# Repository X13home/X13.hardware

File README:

X13.hardware
===========

Hardware section for project X13.Home.
Automation System oriented to "Smart House" over MQTT(S) protocol

Bridge        Bridges between protocols and bus's
Mainboards    Transceivers, Nodes/Gateways and accessories
Obsolete      No comments
Other         Expansions module, modular 72mm series
Sensors       Sensors, Temperature Humidity Pressure ...

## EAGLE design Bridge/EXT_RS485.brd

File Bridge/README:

X13.hardware.Bridge
===================

Bridges between protocols and bus's

Bridge_PCA9517      I2C to I2C Bridge/Level Translator
EXT_RS485           Adapter to RS485 Bus, Modular 72mm Series
EXT_TWI_LVC         I2C to I2C Bridge/Level Translator, Modular 72mm Series
USB_Adapter         USB Adapter to UART adapter 20 pin

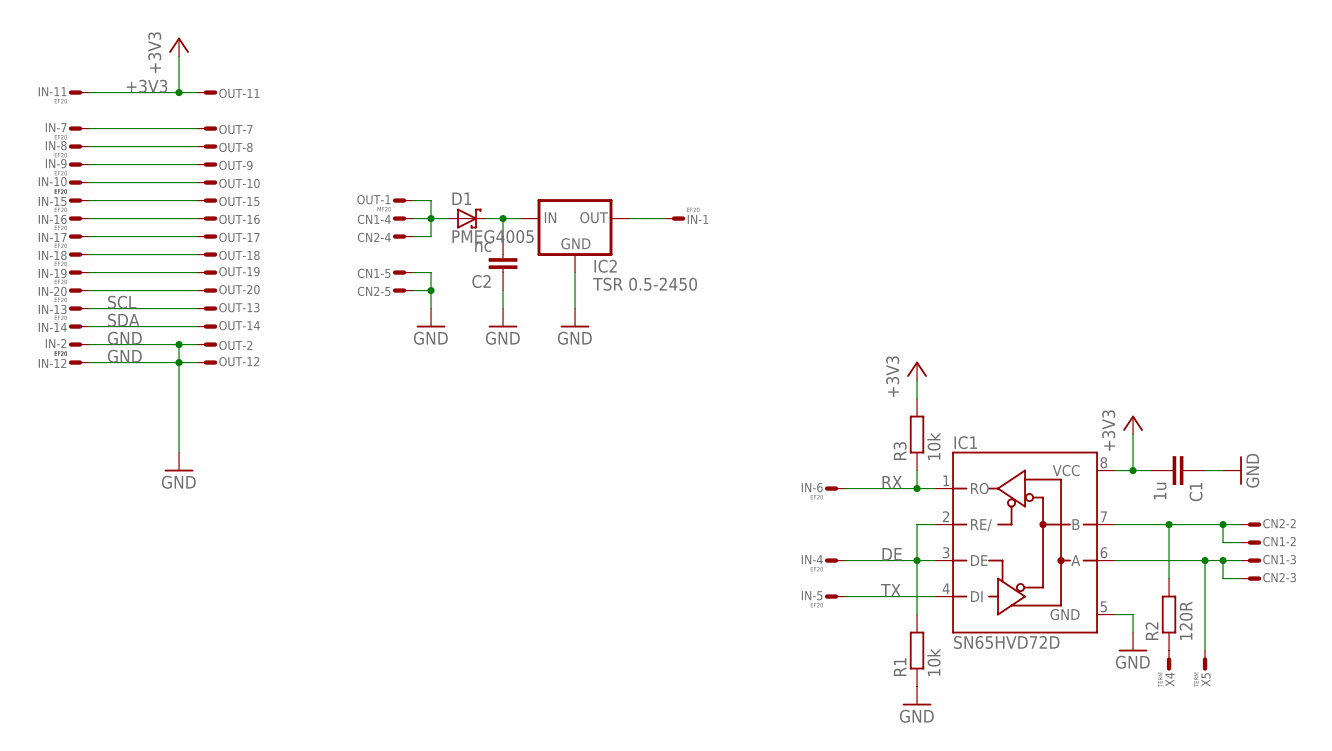
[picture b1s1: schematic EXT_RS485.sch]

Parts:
C1: 1u; 0603
C2: nc; 1206
CN1, CN2: RJ11; 69254
D1: PMEG4005; SOD323
IC1: SN65HVD72D; SOIC8
IC2: TSR 0.5-2450; SIP3
IN: EF20; FE10-2WSS
OUT: MF20; ML20LS
R1, R3: 10k; 0603
R2: 120R; 0603
X4, X5: TERM; T1.6/0.9

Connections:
+3V3: C1.2, IC1.8 (VCC), IN.P$11, OUT.P$11, R3.2
BUS-A: CN1.-3, CN2.-3, IC1.6 (A), X5.1
BUS-B: CN1.-2, CN2.-2, IC1.7 (B), R2.2
BUS-R: R2.1, X4.1
DE: IC1.2 (RE/), IC1.3 (DE), IN.P$4, R1.2
GND: C1.1, C2.1, CN1.-5, CN2.-5, IC1.5 (GND), IC2.P$2 (GND), IN.P$2, IN.P$12, OUT.P$2, OUT.P$12, R1.1
unnamed: IN.P$7, OUT.P$7
unnamed: IN.P$8, OUT.P$8
unnamed: IN.P$9, OUT.P$9
unnamed: IN.P$10, OUT.P$10
unnamed: IN.P$20, OUT.P$20
unnamed: IN.P$19, OUT.P$19
unnamed: IN.P$18, OUT.P$18
unnamed: IN.P$17, OUT.P$17
unnamed: IN.P$16, OUT.P$16
unnamed: IN.P$15, OUT.P$15
unnamed: C2.2, D1.C, IC2.P$1 (IN)
RX: IC1.1 (RO), IN.P$6, R3.1
SCL: IN.P$13, OUT.P$13
SDA: IN.P$14, OUT.P$14
TX: IC1.4 (DI), IN.P$5
VIN: CN1.-4, CN2.-4, D1.A, OUT.P$1
VOUT: IC2.P$3 (OUT), IN.P$1

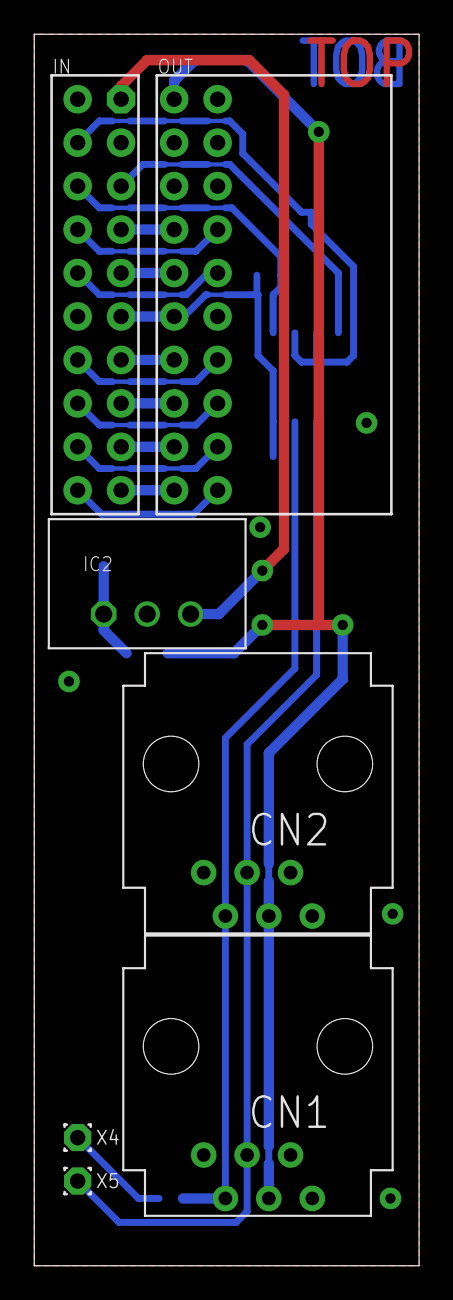
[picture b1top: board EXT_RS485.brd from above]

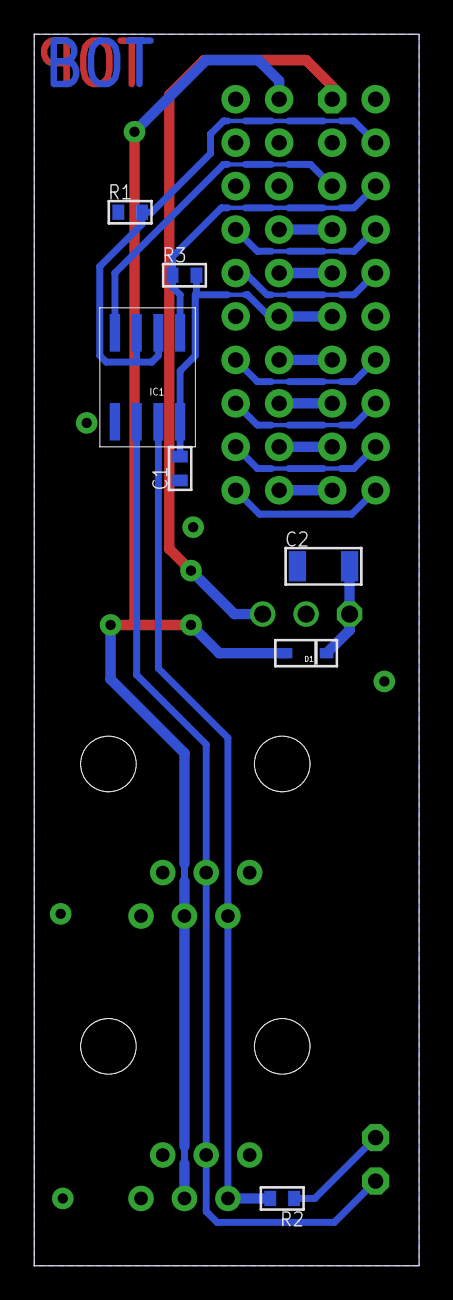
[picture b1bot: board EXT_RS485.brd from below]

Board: 2 copper layers, 22.5 x 72.0 mm, 14 parts (7 on the bottom side), 23 nets.

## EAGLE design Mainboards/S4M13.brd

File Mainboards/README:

X13.hardware.Mainboards
=======================

Hardware section for project X13.Home.

Automation System oriented to "Smart House"(IoT) over MQTT(SN) protocol

Universal
  S2EC13                Universal Mainboard, STM32Fxx + Board ENC28J60/UART-USB/RS485 + RF CC1101(TI), Format DIN 72mm.
  S2ER13                Universal Mainboard, STM32Fxx + Board ENC28J60/UART-USB/RS485 + RF RFM69CW, Format DIN 72mm.
  S2Mn10                Micro (33/19mm) RS485 node, STM32FxxxKxT
  S4Cx11                Mini Board STM32F3 + CC1101 Module
  S4Qx11                Mini Board STM32F3 + RFM69CW Module

RF only 433/868/915 MHz
  TRV_UP20              Mainboard UP20, ATMega328P + TRV CC1101(TI)
  TRV_MRF49_U_V1.1_F    Mainboard UN10, ATMega328P + TRV MRF49XA(Microchip)

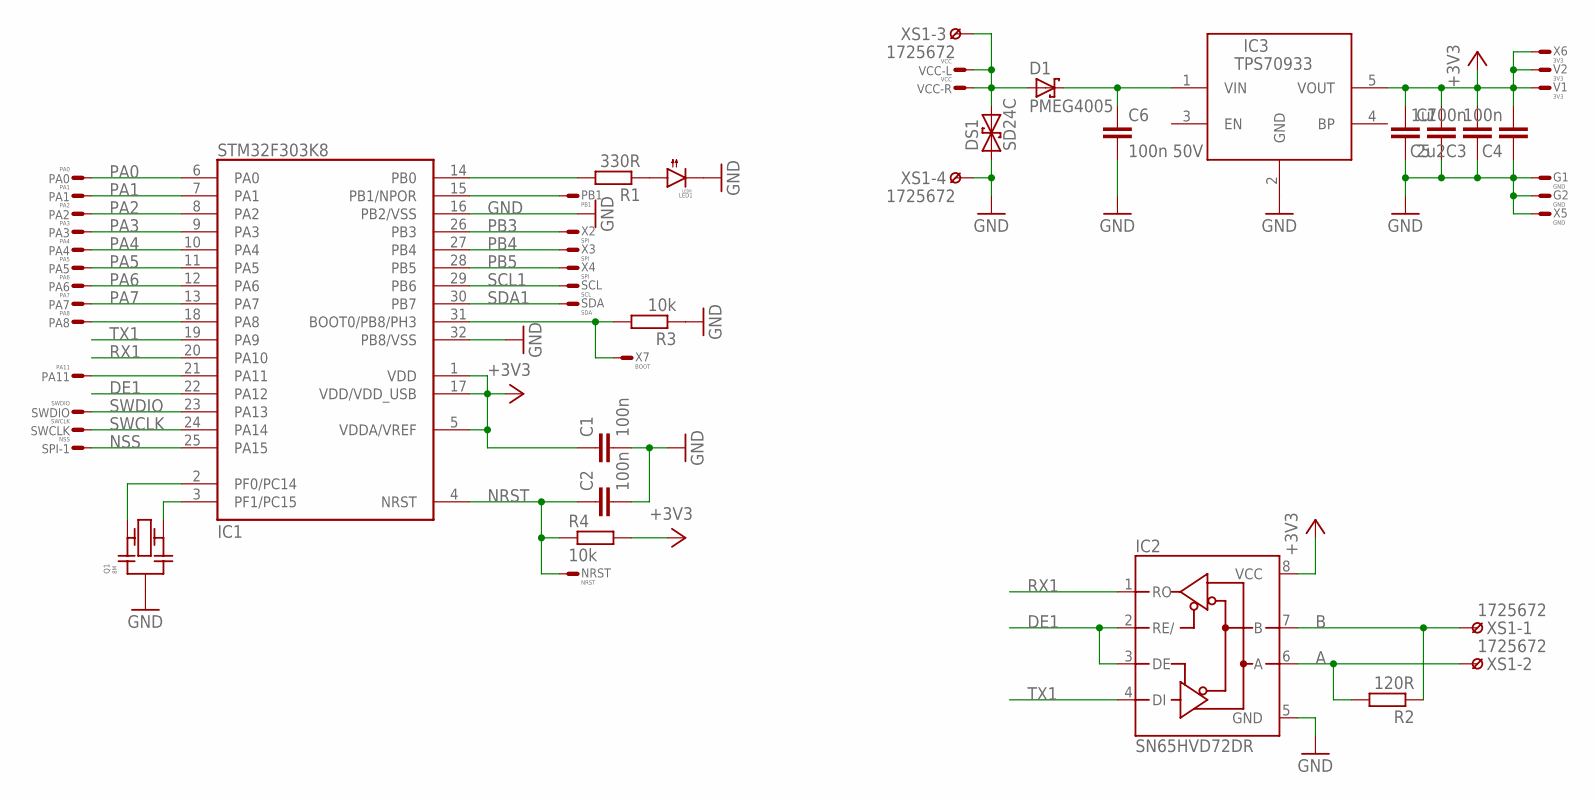
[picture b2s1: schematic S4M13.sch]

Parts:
C1, C2, C3, C4: 100n; 0603
C5: 1u; 0603
C6: 100n 50V; 0603
C7: 2u2; 0603
D1: PMEG4005; SOD323
DS1: SD24C; SOD323
G1, G2: GND; T1.6/0.9
IC1: STM32F303K8; LQFP32-7X7
IC2: SN65HVD72DR; SOIC8
IC3: TPS70933; SOT23-5
LED1: LEDR; 1206
NRST: NRST; T1.6/0.9
PA0: PA0; T1.6/0.9
PA1: PA1; T1.6/0.9
PA2: PA2; T1.6/0.9
PA3: PA3; T1.6/0.9
PA4: PA4; T1.6/0.9
PA5: PA5; T1.6/0.9
PA6: PA6; T1.6/0.9
PA7: PA7; T1.6/0.9
PA8: PA8; T1.6/0.9
PA11: PA11; T1.6/0.9
PB1: PB1; T1.6/0.9
Q1: 8M; CSTCE
R1: 330R; 0603
R2: 120R; 0603
R3, R4: 10k; 0603
SCL: SCL; T1.6/0.9
SDA: SDA; T1.6/0.9
SPI-1: NSS; S1.6/0.8
SWCLK: SWCLK; T1.6/0.9
SWDIO: SWDIO; T1.6/0.9
V1, V2: 3V3; T1.6/0.9
VCC-L: VCC; T1.6/0.9
VCC-R: VCC; T1.6/0.9
X2, X3, X4: SPI; S1.6/0.8
X5: GND; S1.6/0.8
X6: 3V3; S1.6/0.8
X7: BOOT; S1.27R
XS1: 1725672

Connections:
+3V3: C1.1, C3.2, C4.2, C5.2, C7.1, IC1.1 (VDD), IC1.5 (VDDA/VREF), IC1.17 (VDD/VDD_USB), IC2.8 (VCC), IC3.5 (VOUT), R4.2, V1.1, V2.1, X6.W
A: IC2.6 (A), R2.2, XS1.2
B: IC2.7 (B), R2.1, XS1.1
DE1: IC1.22 (PA12), IC2.2 (RE/), IC2.3 (DE)
GND: C1.2, C2.2, C3.1, C4.1, C5.1, C6.2, C7.2, DS1.A (1), G1.1, G2.1, IC1.16 (PB2/VSS), IC1.32 (PB8/VSS), IC2.5 (GND), IC3.2 (GND), LED1.2 (C), Q1.G (M), R3.1, X5.W, XS1.4
LED: IC1.14 (PB0), R1.2
unnamed: IC1.3 (PF1/PC15), Q1.B (2)
unnamed: IC1.31 (BOOT0/PB8/PH3), R3.2, X7.1
unnamed: IC1.2 (PF0/PC14), Q1.A (1)
unnamed: C6.1, D1.C, IC3.1 (VIN)
unnamed: LED1.1 (A), R1.1
NRST: C2.1, IC1.4 (NRST), NRST.1, R4.1
NSS: IC1.25 (PA15), SPI-1.W
PA0: IC1.6 (PA0), PA0.1
PA1: IC1.7 (PA1), PA1.1
PA2: IC1.8 (PA2), PA2.1
PA3: IC1.9 (PA3), PA3.1
PA4: IC1.10 (PA4), PA4.1
PA5: IC1.11 (PA5), PA5.1
PA6: IC1.12 (PA6), PA6.1
PA7: IC1.13 (PA7), PA7.1
PA8: IC1.18 (PA8), PA8.1
PA11: IC1.21 (PA11), PA11.1
PB1: IC1.15 (PB1/NPOR), PB1.1
PB3: IC1.26 (PB3), X2.W
PB4: IC1.27 (PB4), X3.W
PB5: IC1.28 (PB5), X4.W
RX1: IC1.20 (PA10), IC2.1 (RO)
SCL1: IC1.29 (PB6), SCL.1
SDA1: IC1.30 (PB7), SDA.1
SWCLK: IC1.24 (PA14), SWCLK.1
SWDIO: IC1.23 (PA13), SWDIO.1
TX1: IC1.19 (PA9), IC2.4 (DI)
VIN: D1.A, DS1.C (2), VCC-L.1, VCC-R.1, XS1.3

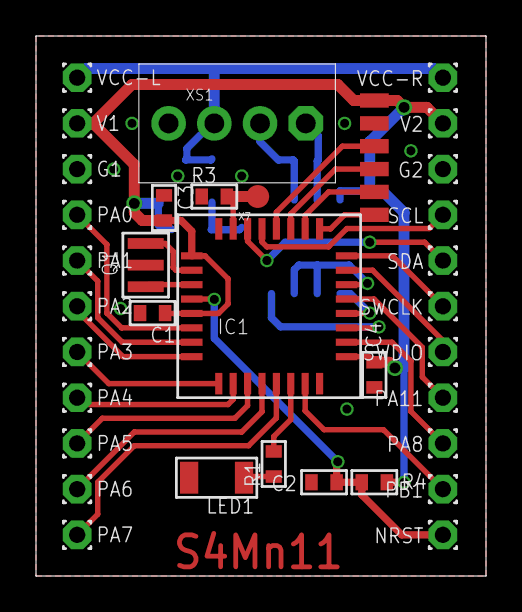
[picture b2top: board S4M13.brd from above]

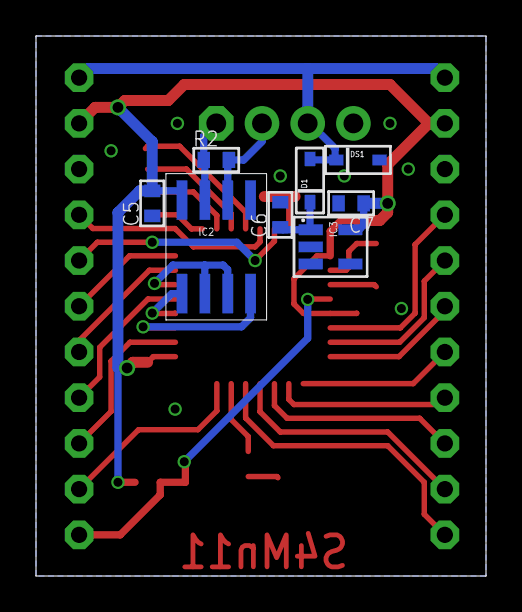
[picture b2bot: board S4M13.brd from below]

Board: 2 copper layers, 25.0 x 30.0 mm, 48 parts (8 on the bottom side), 34 nets.

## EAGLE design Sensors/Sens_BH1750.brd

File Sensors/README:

Sens_BH1750(small)          Sensor Rohm - BH1750, Ambient Light
Sens_BMP180                 Sensor Bosh - BMP180, Pressure & Temperature, compatible with BMP085
Sens_BME280                 Sensor Bosh - BME280, Pressure Temperature Humidity
Sens_CC2D                   Sensor ChipCap2 from "GE Measurement & Control", Temperature and Humidity
Sens_HIH613x                Sensors Honeywell - HIH6130/HIH6131, Temperature and Humidity
Sens_LM75                   Sensor NXP/NS/STmicro - LM75, Temperature
Sens_SHT2x                  Sensor Sensirion SHT21/SiLabs Si7020, Temperature and Humidity

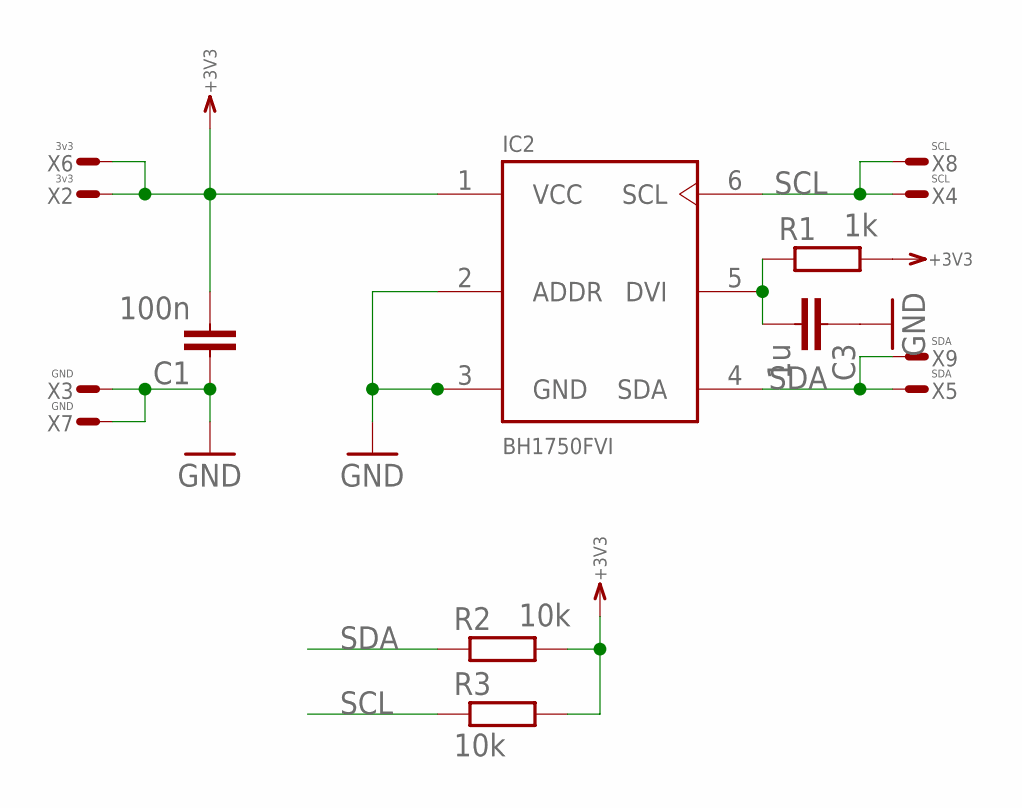
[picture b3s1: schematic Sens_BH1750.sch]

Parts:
C1: 100n; 0603
C3: 1u; 0603
IC2: BH1750FVI; WSOF6I
R1: 1k; 0603
R2, R3: 10k; 0603
X2, X6: 3v3; T1.6/0.9
X3, X7: GND; T1.6/0.9
X4, X8: SCL; T1.6/0.9
X5, X9: SDA; T1.6/0.9

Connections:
+3V3: C1.2, IC2.1 (VCC), R1.2, R2.2, R3.2, X2.1, X6.1
GND: C1.1, C3.1, IC2.2 (ADDR), IC2.3 (GND), X3.1, X7.1
unnamed: C3.2, IC2.5 (DVI), R1.1
SCL: IC2.6 (SCL), R3.1, X4.1, X8.1
SDA: IC2.4 (SDA), R2.1, X5.1, X9.1

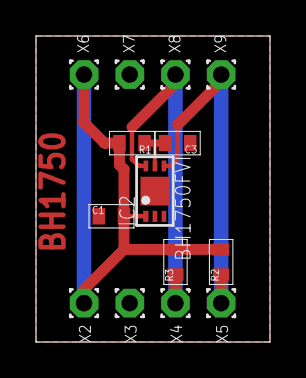
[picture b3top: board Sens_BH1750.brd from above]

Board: 2 copper layers, 13.0 x 17.0 mm, 14 parts (0 on the bottom side), 5 nets.

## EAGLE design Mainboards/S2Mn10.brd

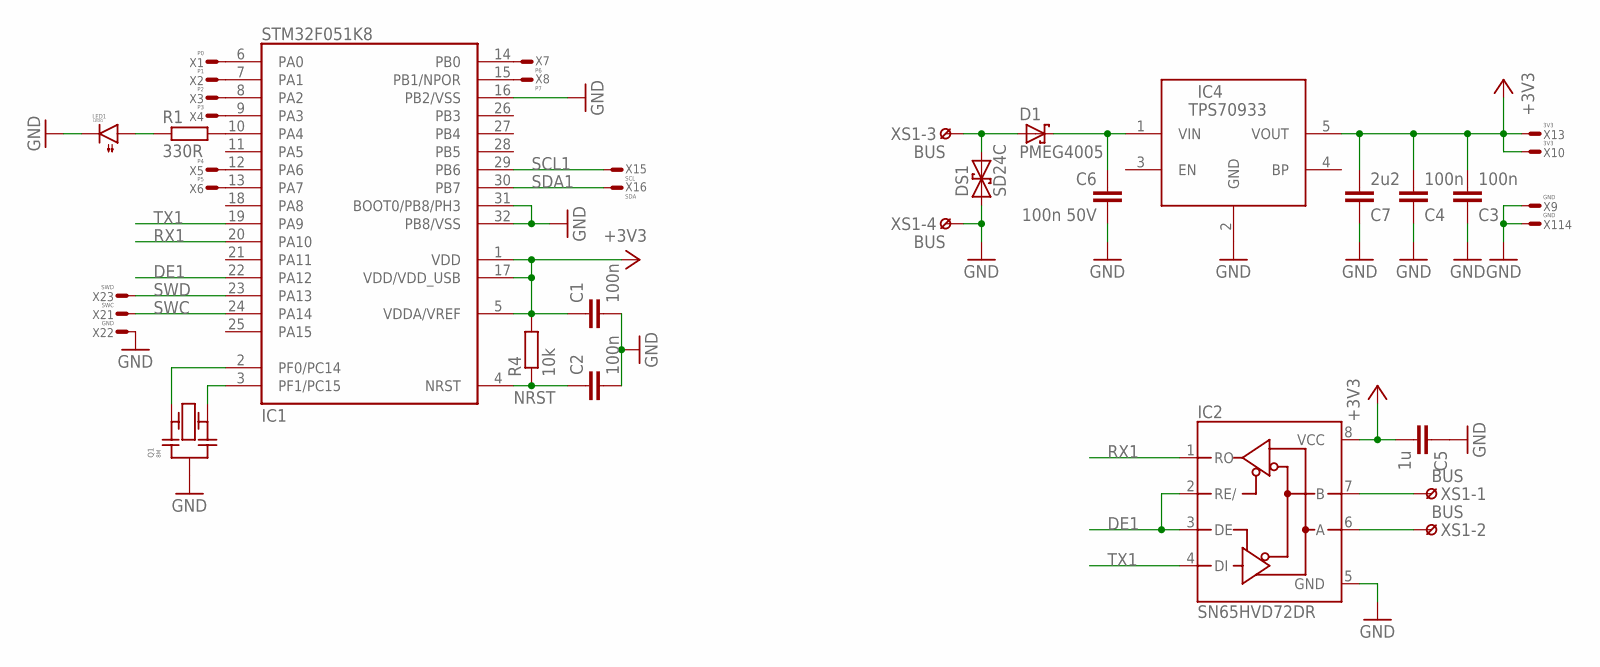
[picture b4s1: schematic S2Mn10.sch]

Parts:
C1, C2, C3, C4: 100n; 0603
C5: 1u; 0603
C6: 100n 50V; 0603
C7: 2u2; 0603
D1: PMEG4005; SOD323
DS1: SD24C; SOD323
IC1: STM32F051K8; LQFP32-7X7
IC2: SN65HVD72DR; SOIC8
IC4: TPS70933; SOT23-5
LED1: LEDG; 1206
Q1: 8M; CSTCE
R1: 330R; 0603
R4: 10k; 0603
X1: P0; T1.6/0.9
X2: P1; T1.6/0.9
X3: P2; T1.6/0.9
X4: P3; T1.6/0.9
X5: P4; T1.6/0.9
X6: P5; T1.6/0.9
X7: P6; T1.6/0.9
X8: P7; T1.6/0.9
X9, X22, X114: GND; T1.6/0.9
X10, X13: 3V3; T1.6/0.9
X15: SCL; T1.6/0.9
X16: SDA; T1.6/0.9
X21: SWC; T1.6/0.9
X23: SWD; T1.6/0.9
XS1: BUS; 1725672

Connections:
+3V3: C1.1, C3.2, C4.2, C5.2, C7.2, IC1.1 (VDD), IC1.5 (VDDA/VREF), IC1.17 (VDD/VDD_USB), IC2.8 (VCC), IC4.5 (VOUT), R4.2, X10.1, X13.1
DE1: IC1.22 (PA12), IC2.2 (RE/), IC2.3 (DE)
GND: C1.2, C2.2, C3.1, C4.1, C5.1, C6.2, C7.1, DS1.A (1), IC1.16 (PB2/VSS), IC1.31 (BOOT0/PB8/PH3), IC1.32 (PB8/VSS), IC2.5 (GND), IC4.2 (GND), LED1.2 (C), Q1.G (M), X9.1, X22.1, X114.1, XS1.4
LED: IC1.10 (PA4), R1.2
unnamed: IC2.6 (A), XS1.2
unnamed: IC1.3 (PF1/PC15), Q1.B (2)
unnamed: IC2.7 (B), XS1.1
unnamed: IC1.6 (PA0), X1.1
unnamed: IC1.2 (PF0/PC14), Q1.A (1)
unnamed: IC1.7 (PA1), X2.1
unnamed: IC1.8 (PA2), X3.1
unnamed: IC1.9 (PA3), X4.1
unnamed: IC1.12 (PA6), X5.1
unnamed: IC1.13 (PA7), X6.1
unnamed: IC1.14 (PB0), X7.1
unnamed: IC1.15 (PB1/NPOR), X8.1
unnamed: D1.A, DS1.C (2), XS1.3
unnamed: LED1.1 (A), R1.1
unnamed: C6.1, D1.C, IC4.1 (VIN)
NRST: C2.1, IC1.4 (NRST), R4.1
RX1: IC1.20 (PA10), IC2.1 (RO)
SCL1: IC1.29 (PB6), X15.1
SDA1: IC1.30 (PB7), X16.1
SWC: IC1.24 (PA14), X21.1
SWD: IC1.23 (PA13), X23.1
TX1: IC1.19 (PA9), IC2.4 (DI)

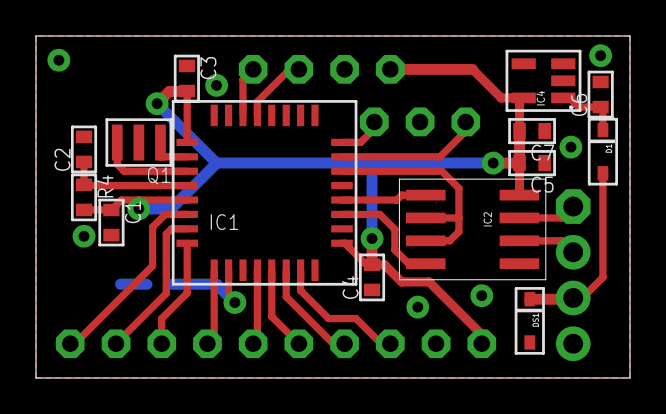
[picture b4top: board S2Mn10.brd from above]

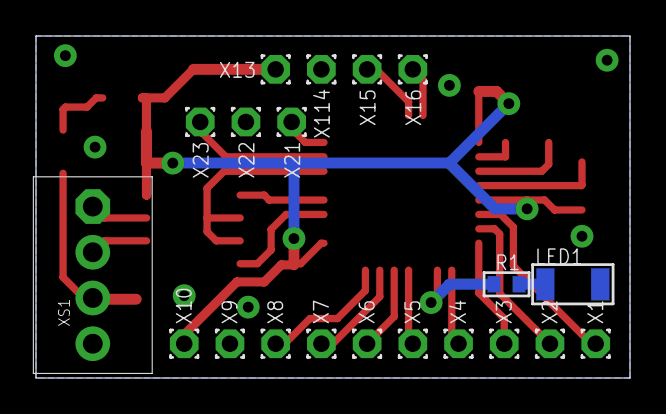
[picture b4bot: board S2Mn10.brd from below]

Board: 2 copper layers, 33.0 x 19.0 mm, 34 parts (20 on the bottom side), 26 nets.

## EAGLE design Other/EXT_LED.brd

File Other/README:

Extensions Module, Modular Series
  EXT_ADIN              Universal ADIO board
  EXT_DC_OUT            Digital Outs 4x 10-40V 1A
  EXT_DIMMER            AC Dimmer 2channels
  EXT_EXPANDER          I2C Bus expander to 16 digital IO, IC - MCP23016
  EXT_LED               Debug Indicators Board
  EXT_LED_RGB_NPN       RGB LED Driver with NPN outs, Analog - BlinkM, Prototype
  EXT_SCR               4x AC SCR Switch 80-300VAC, 2/8A

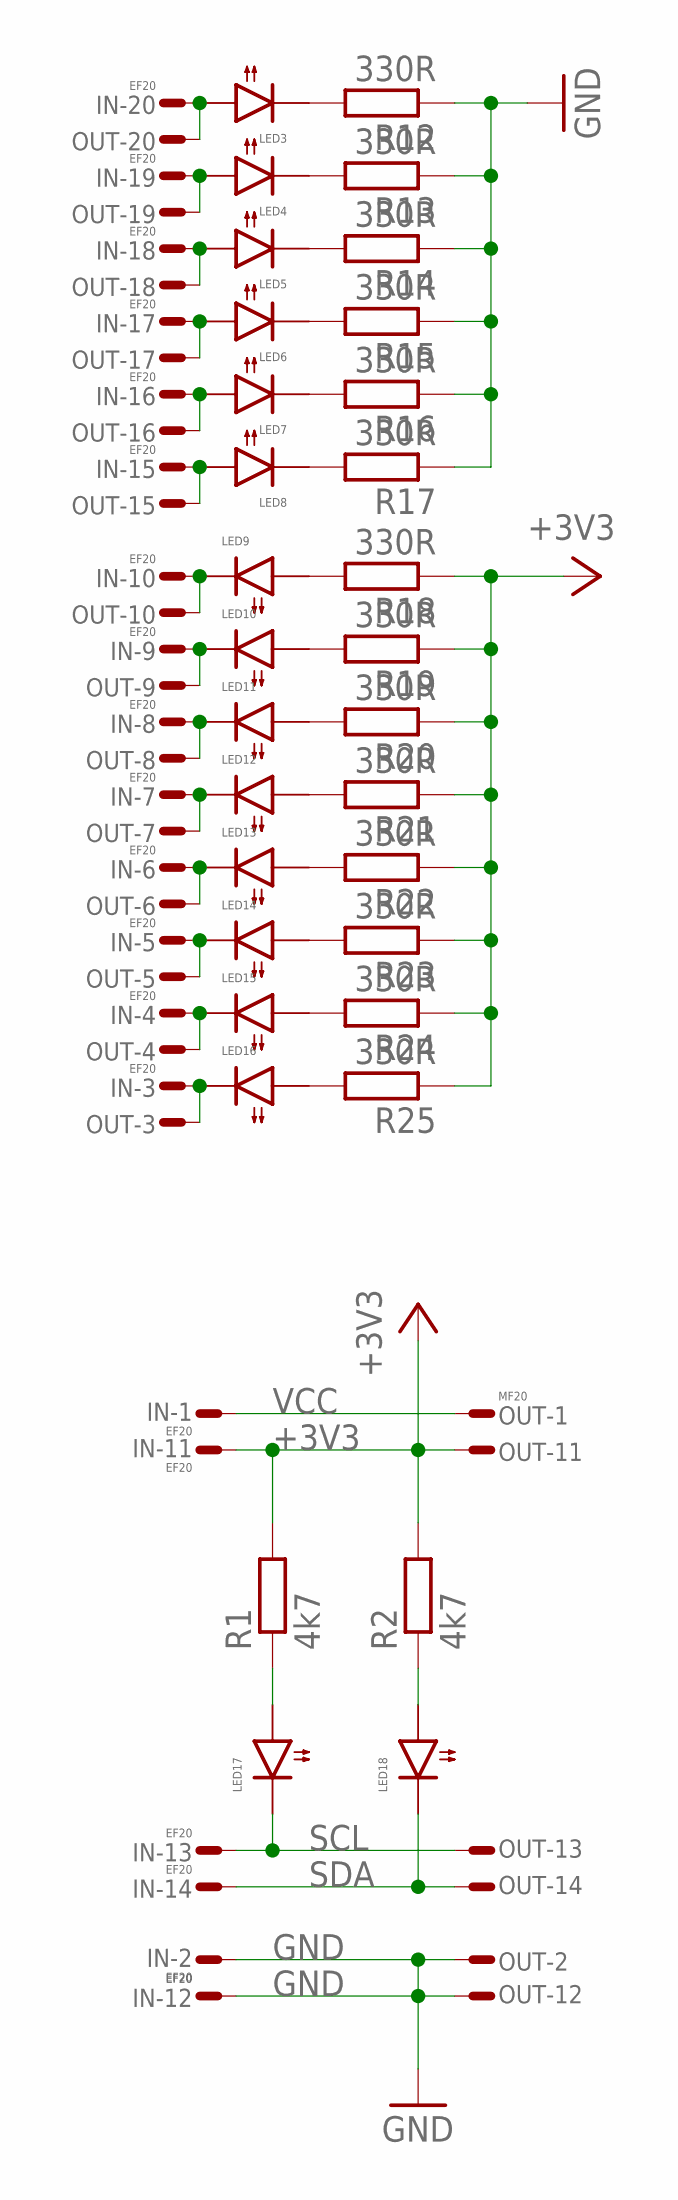
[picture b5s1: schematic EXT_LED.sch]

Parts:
IN: EF20; FE10-2WSS
LED3, LED4, LED5, LED6, LED7, LED8, LED9, LED10, LED11, LED12, LED13, LED14, LED15, LED16, LED17, LED18: LED0603; 0603
OUT: MF20; ML20LS
R1, R2: 4k7; 0603
R12, R13, R14, R15, R16, R17, R18, R19, R20, R21, R22, R23, R24, R25: 330R; 0603

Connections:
+3V3: IN.P$11, OUT.P$11, R1.2, R2.2, R18.1, R19.1, R20.1, R21.1, R22.1, R23.1, R24.1, R25.1
GND: IN.P$2, IN.P$12, OUT.P$2, OUT.P$12, R12.1, R13.1, R14.1, R15.1, R16.1, R17.1
unnamed: IN.P$19, LED4.1 (A), OUT.P$19
unnamed: IN.P$20, LED3.1 (A), OUT.P$20
unnamed: LED17.1 (A), R1.1
unnamed: LED18.1 (A), R2.1
unnamed: IN.P$10, LED9.2 (C), OUT.P$10
unnamed: LED9.1 (A), R18.2
unnamed: LED10.1 (A), R19.2
unnamed: LED11.1 (A), R20.2
unnamed: LED12.1 (A), R21.2
unnamed: LED13.1 (A), R22.2
unnamed: LED14.1 (A), R23.2
unnamed: LED15.1 (A), R24.2
unnamed: LED3.2 (C), R12.2
unnamed: LED16.1 (A), R25.2
unnamed: LED4.2 (C), R13.2
unnamed: LED5.2 (C), R14.2
unnamed: LED6.2 (C), R15.2
unnamed: LED7.2 (C), R16.2
unnamed: LED8.2 (C), R17.2
unnamed: IN.P$18, LED5.1 (A), OUT.P$18
unnamed: IN.P$17, LED6.1 (A), OUT.P$17
unnamed: IN.P$16, LED7.1 (A), OUT.P$16
unnamed: IN.P$15, LED8.1 (A), OUT.P$15
unnamed: IN.P$9, LED10.2 (C), OUT.P$9
unnamed: IN.P$8, LED11.2 (C), OUT.P$8
unnamed: IN.P$7, LED12.2 (C), OUT.P$7
unnamed: IN.P$6, LED13.2 (C), OUT.P$6
unnamed: IN.P$5, LED14.2 (C), OUT.P$5
unnamed: IN.P$4, LED15.2 (C), OUT.P$4
unnamed: IN.P$3, LED16.2 (C), OUT.P$3
SCL: IN.P$13, LED17.2 (C), OUT.P$13
SDA: IN.P$14, LED18.2 (C), OUT.P$14
VCC: IN.P$1, OUT.P$1

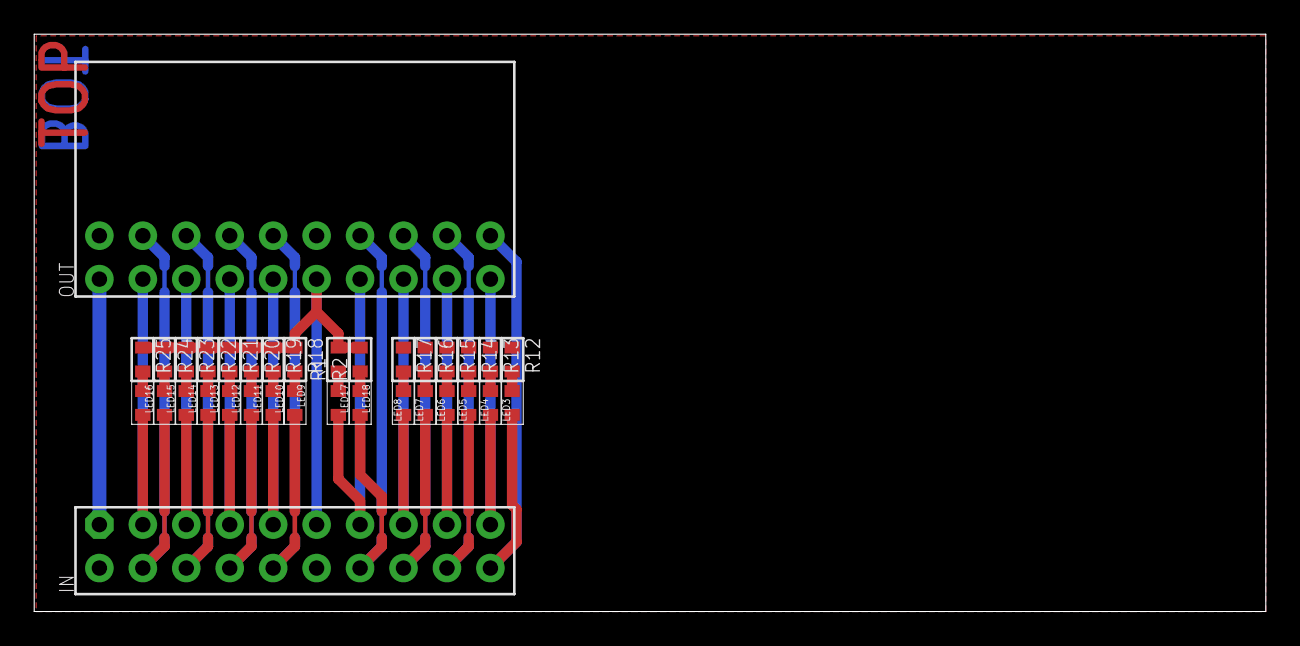
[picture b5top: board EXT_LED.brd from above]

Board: 2 copper layers, 72.0 x 33.8 mm, 34 parts (0 on the bottom side), 35 nets.

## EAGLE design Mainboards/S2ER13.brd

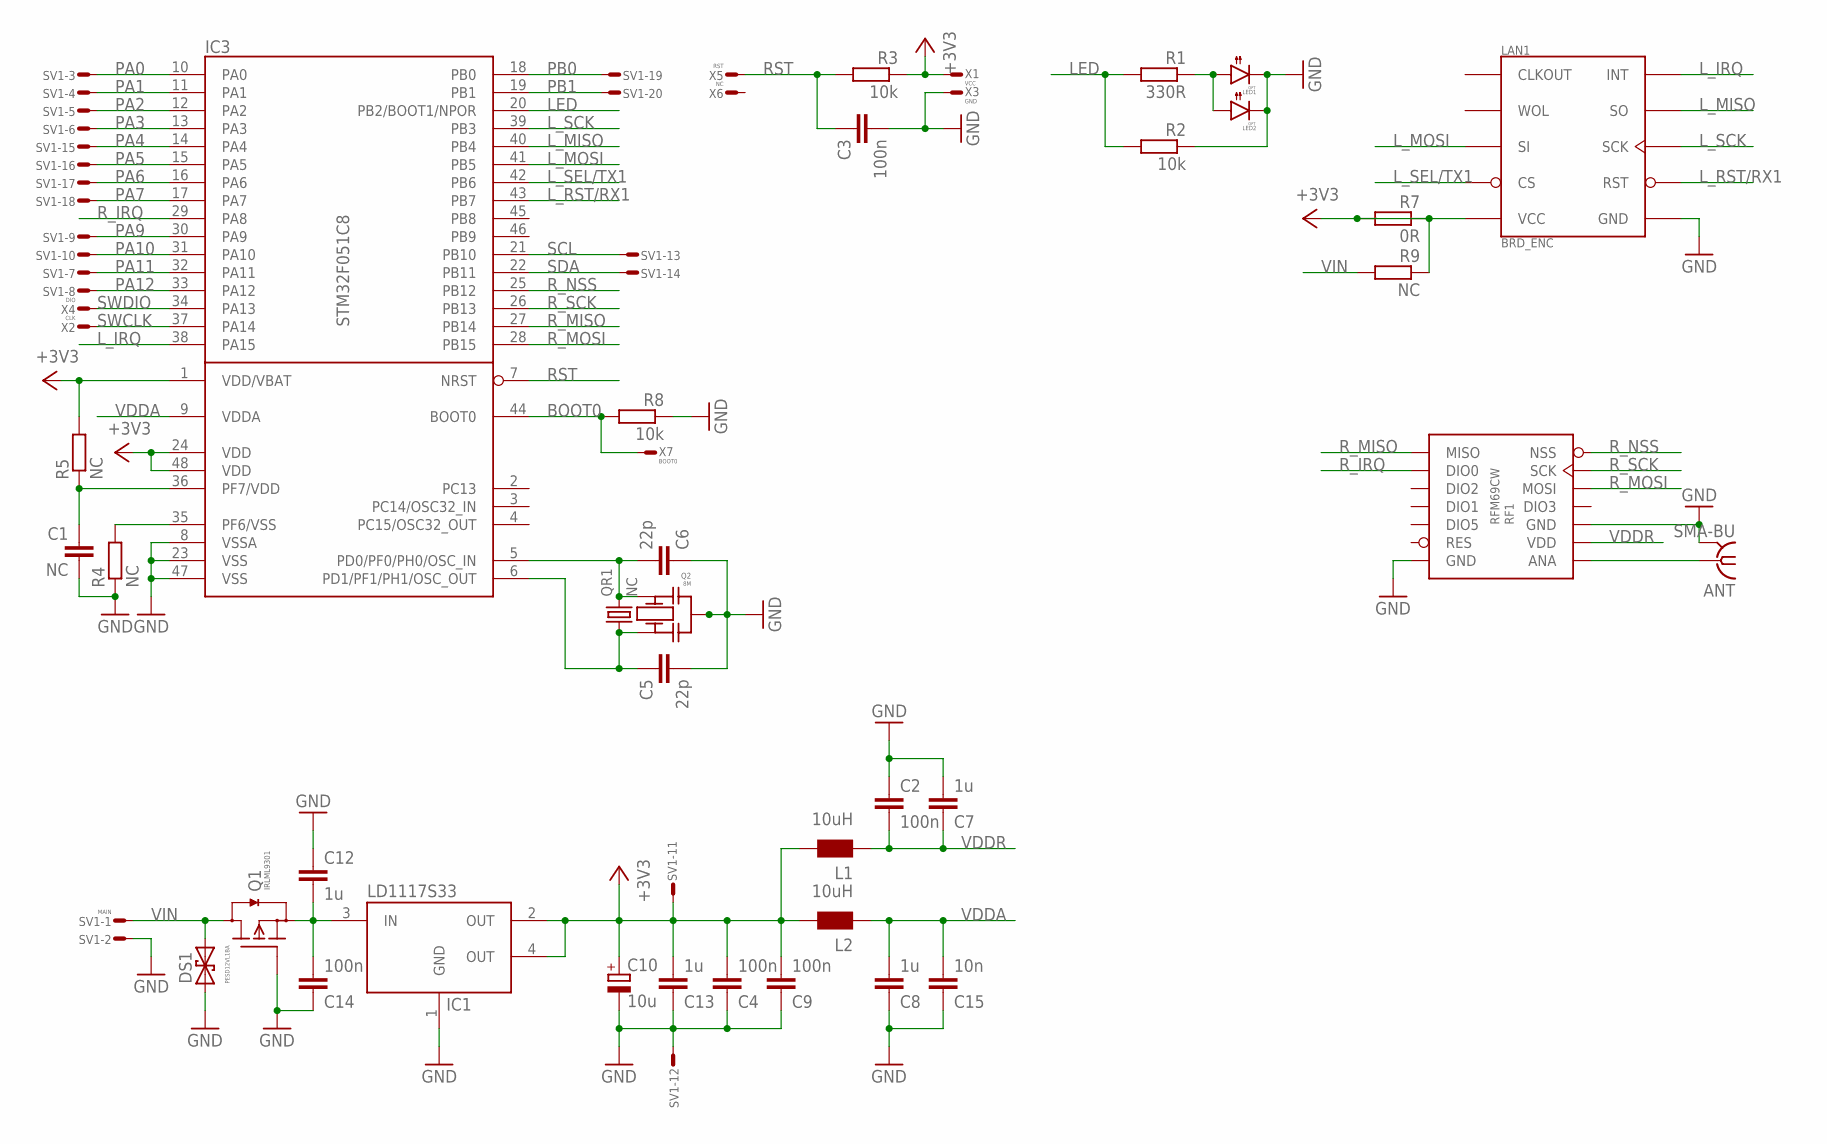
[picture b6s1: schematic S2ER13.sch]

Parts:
ANT: SMA-BU; BU-SMA-V
C1: NC; 0603
C2, C3, C4, C9, C14: 100n; 0603
C5, C6: 22p; 0603
C7, C8, C12, C13: 1u; 0603
C10: 10u; SMC_A
C15: 10n; 0603
DS1: PESD12VL1BA; SOD323
IC1: LD1117S33; SOT223
IC3: STM32F051C8; LQFP48
L1, L2: 10uH; 0603
LAN1: BRD_ENC
LED1: OPT; T1-3/4
LED2: OPT; 1206
Q1: IRLML9301; SOT23
Q2: 8M; CSTCE
QR1: NC; ABS07
R1: 330R; 0603
R2, R3, R8: 10k; 0603
R4, R5, R9: NC; 0603
R7: 0R; 0603
RF1: RFM69CW
SV1: MAIN; ML20LS
X1: VCC; T1.6/0.9
X2: CLK; T1.6/0.9
X3: GND; T1.6/0.9
X4: DIO; T1.6/0.9
X5: RST; T1.6/0.9
X6: NC; T1.6/0.9
X7: BOOT0; T1.6/0.9

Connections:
+3V3: C4.2, C9.2, C10.+, C13.2, IC1.2 (OUT), IC1.4 (OUT), IC3.1 (VDD/VBAT), IC3.24 (VDD), IC3.48 (VDD), L1.2, L2.2, LAN1.P$9 (VCC), R3.1, R5.2, R7.1, R7.2, R9.1, SV1.P$11, X1.1
BOOT0: IC3.44 (BOOT0), R8.2, X7.1
GND: ANT.2, ANT.3 (2), ANT.4 (2), ANT.5 (2), C1.2, C2.1, C3.2, C4.1, C5.2, C6.1, C7.2, C8.1, C9.1, C10.-, C12.1, C13.1, C14.1, C15.1, DS1.A (1), IC1.1 (GND), IC3.8 (VSSA), IC3.23 (VSS), IC3.47 (VSS), LAN1.P$10 (GND), LED1.C, LED2.2 (C), Q1.1 (G), Q2.G (M), R2.1, R4.1, R8.1, RF1.GND@3 (GND), RF1.GND@14 (GND), SV1.P$2, SV1.P$12, X3.1
LED: IC3.20 (PB2/BOOT1/NPOR), R1.2, R2.2
L_IRQ: IC3.38 (PA15), LAN1.P$2 (INT)
L_MISO: IC3.40 (PB4), LAN1.P$4 (SO)
L_MOSI: IC3.41 (PB5), LAN1.P$5 (SI)
L_RST/RX1: IC3.43 (PB7), LAN1.P$8 (RST)
L_SCK: IC3.39 (PB3), LAN1.P$6 (SCK)
L_SEL/TX1: IC3.42 (PB6), LAN1.P$7 (CS)
unnamed: LED1.A, LED2.1 (A), R1.1
unnamed: IC3.35 (PF6/VSS), R4.2
unnamed: C1.1, IC3.36 (PF7/VDD), R5.1
unnamed: ANT.1, RF1.ANA
unnamed: C6.2, IC3.5 (PD0/PF0/PH0/OSC_IN), Q2.A (1), QR1.P$2 (2)
unnamed: C5.1, IC3.6 (PD1/PF1/PH1/OSC_OUT), Q2.B (2), QR1.P$1 (1)
unnamed: C12.2, C14.2, IC1.3 (IN), Q1.2 (S)
PA0: IC3.10 (PA0), SV1.P$3
PA1: IC3.11 (PA1), SV1.P$4
PA2: IC3.12 (PA2), SV1.P$5
PA3: IC3.13 (PA3), SV1.P$6
PA4: IC3.14 (PA4), SV1.P$15
PA5: IC3.15 (PA5), SV1.P$16
PA6: IC3.16 (PA6), SV1.P$17
PA7: IC3.17 (PA7), SV1.P$18
PA9: IC3.30 (PA9), SV1.P$9
PA10: IC3.31 (PA10), SV1.P$10
PA11: IC3.32 (PA11), SV1.P$7
PA12: IC3.33 (PA12), SV1.P$8
PB0: IC3.18 (PB0), SV1.P$19
PB1: IC3.19 (PB1), SV1.P$20
RST: C3.1, IC3.7 (NRST), R3.2, X5.1
R_IRQ: IC3.29 (PA8), RF1.DIO0
R_MISO: IC3.27 (PB14), RF1.MISO
R_MOSI: IC3.28 (PB15), RF1.MOSI
R_NSS: IC3.25 (PB12), RF1.NSS
R_SCK: IC3.26 (PB13), RF1.SCK
SCL: IC3.21 (PB10), SV1.P$13
SDA: IC3.22 (PB11), SV1.P$14
SWCLK: IC3.37 (PA14), X2.1
SWDIO: IC3.34 (PA13), X4.1
VDDA: C8.2, C15.2, IC3.9 (VDDA), L2.1
VDDR: C2.2, C7.1, L1.1, RF1.VDD
VIN: DS1.C (2), Q1.3 (D), R9.2, SV1.P$1

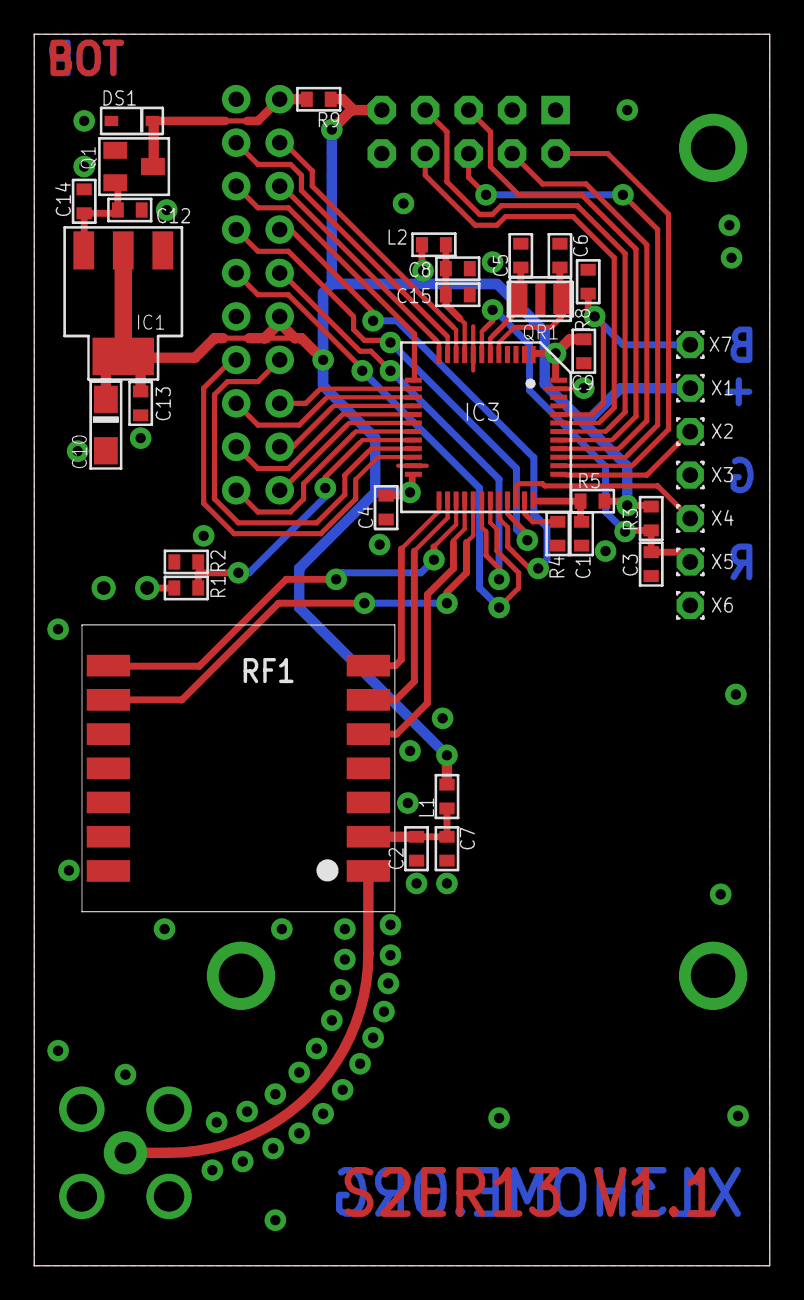
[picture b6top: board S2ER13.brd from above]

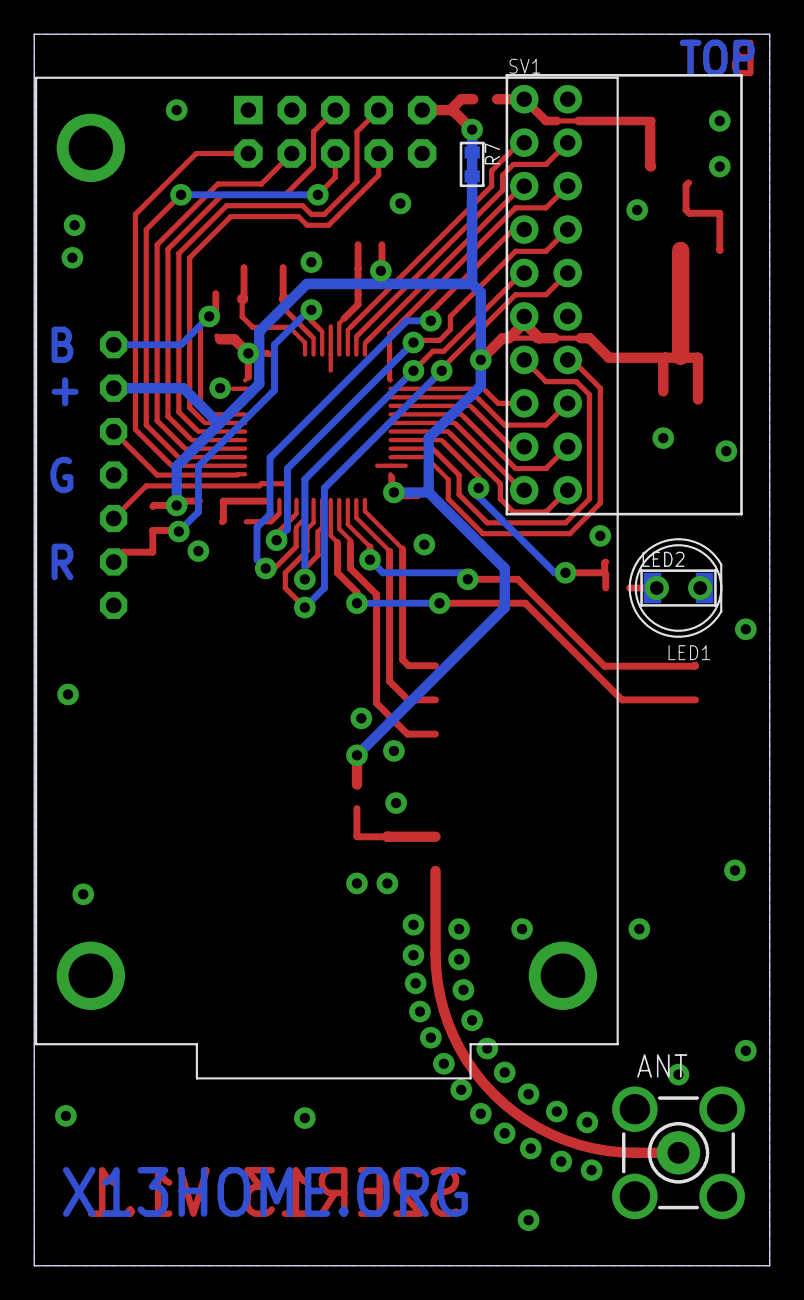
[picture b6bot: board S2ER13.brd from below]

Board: 2 copper layers, 43.0 x 72.0 mm, 43 parts (5 on the bottom side), 44 nets.

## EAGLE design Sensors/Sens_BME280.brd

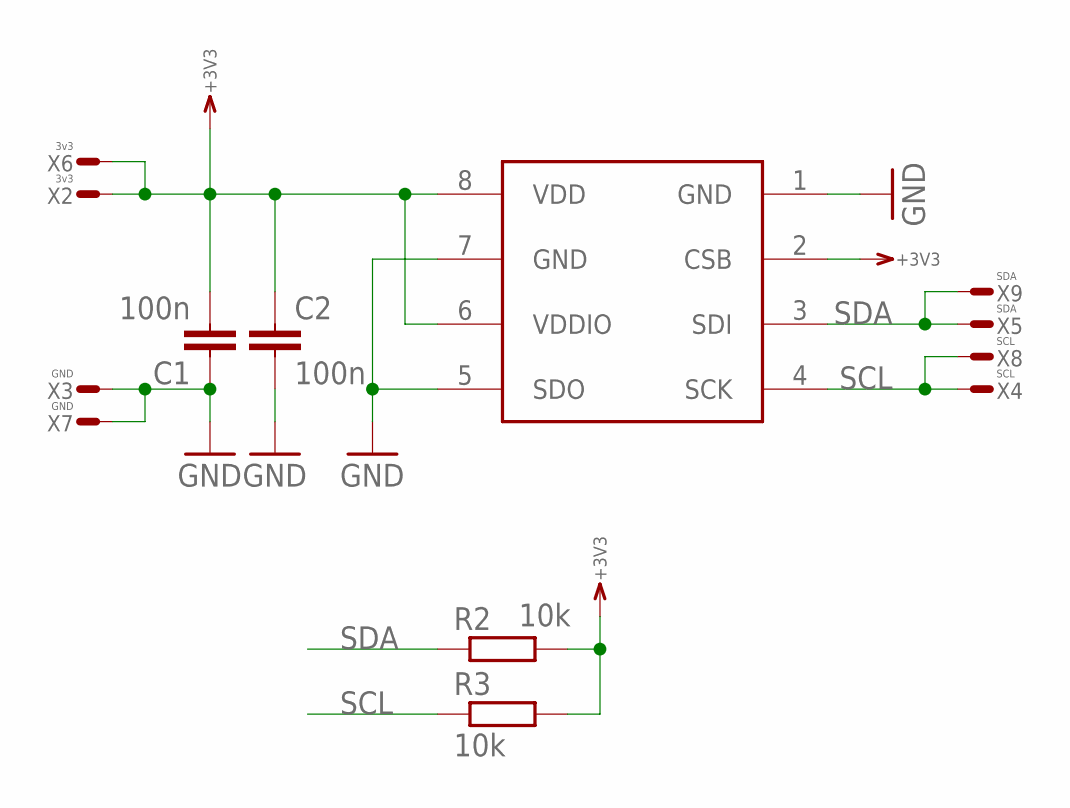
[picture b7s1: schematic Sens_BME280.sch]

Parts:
C1, C2: 100n; 0603
IC1: BME280
R2, R3: 10k; 0603
X2, X6: 3v3; T1.6/0.9
X3, X7: GND; T1.6/0.9
X4, X8: SCL; T1.6/0.9
X5, X9: SDA; T1.6/0.9

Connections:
+3V3: C1.2, C2.1, IC1.2 (CSB), IC1.6 (VDDIO), IC1.8 (VDD), R2.2, R3.2, X2.1, X6.1
GND: C1.1, C2.2, IC1.1 (GND), IC1.5 (SDO), IC1.7 (GND), X3.1, X7.1
SCL: IC1.4 (SCK), R3.1, X4.1, X8.1
SDA: IC1.3 (SDI), R2.1, X5.1, X9.1

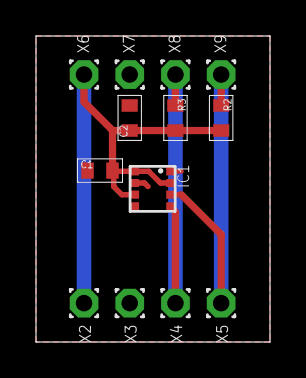
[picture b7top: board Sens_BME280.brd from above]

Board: 2 copper layers, 13.0 x 17.0 mm, 13 parts (0 on the bottom side), 4 nets.

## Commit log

2013-01-18 Detach hardware from X13.wireless section
2013-01-21 Added I2C to 1Wire bridge with DS2482-100
2013-01-22 Typo correction and more elegance presentation
2013-01-28 I2C to I2C bridge/Level translator
2013-01-29 Test
2013-01-29 Added Descriptions
2013-02-12 BMP180 pressure sensor is added instead of the obsolete BMP085
2013-02-24 Readme
2013-03-19 RFM70 + RFM23 Prototypes
2013-03-19 Description
2013-07-02 Added devices
2013-10-25 Added LED RGB Controller prototype for modular version
2013-11-13 Added Temperature and Humidity sensor ChipCap2 from "GE Measurement & Control"
2013-11-13 Added Bus Expander on MCP23016
2013-11-25 Added ...
2013-11-26 Reorganization
2013-12-11 Added PDF Preview
2013-12-13 Optimization
2013-12-20 Optimized R
2014-02-04 Added AC Dimmer
2014-03-25 USB Adepter V1
2015-06-23 Added Sensor Bosh BME280
2015-08-14 Added, universal Mainboard STM32Fxx + LAN(ENC28J60)/UART-USB(CP2102)/RS485 + RF(CC1101)
2015-08-14 S2EC13, corrected R9
2015-08-14 Added S2EC13.pdf
2015-12-04 Added prototypes
2016-01-10 S2ER13 Proto
2016-04-29 Added Board S4CX11
2016-05-04 Added S4QX11
2016-06-20 Minor Changes
2016-06-23 Added RS485 boards
2016-06-26 USB Adapter, to Bridge from Mainboards
2016-07-06 Added LED's
2016-09-27 Updated mainboards
2017-09-19 Added S4M13
